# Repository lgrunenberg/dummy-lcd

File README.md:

dummy-lcd
=========

Files for using the Sony Vivaz Active Dummy LCD

TODO:
  - completely remove Arduino dependencies ( e.g. direct port access instead of pin numbers)
  - TODOs annotated in certain files

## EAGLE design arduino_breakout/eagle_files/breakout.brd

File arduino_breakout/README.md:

Breakout board for Arduino Mega + Example Code

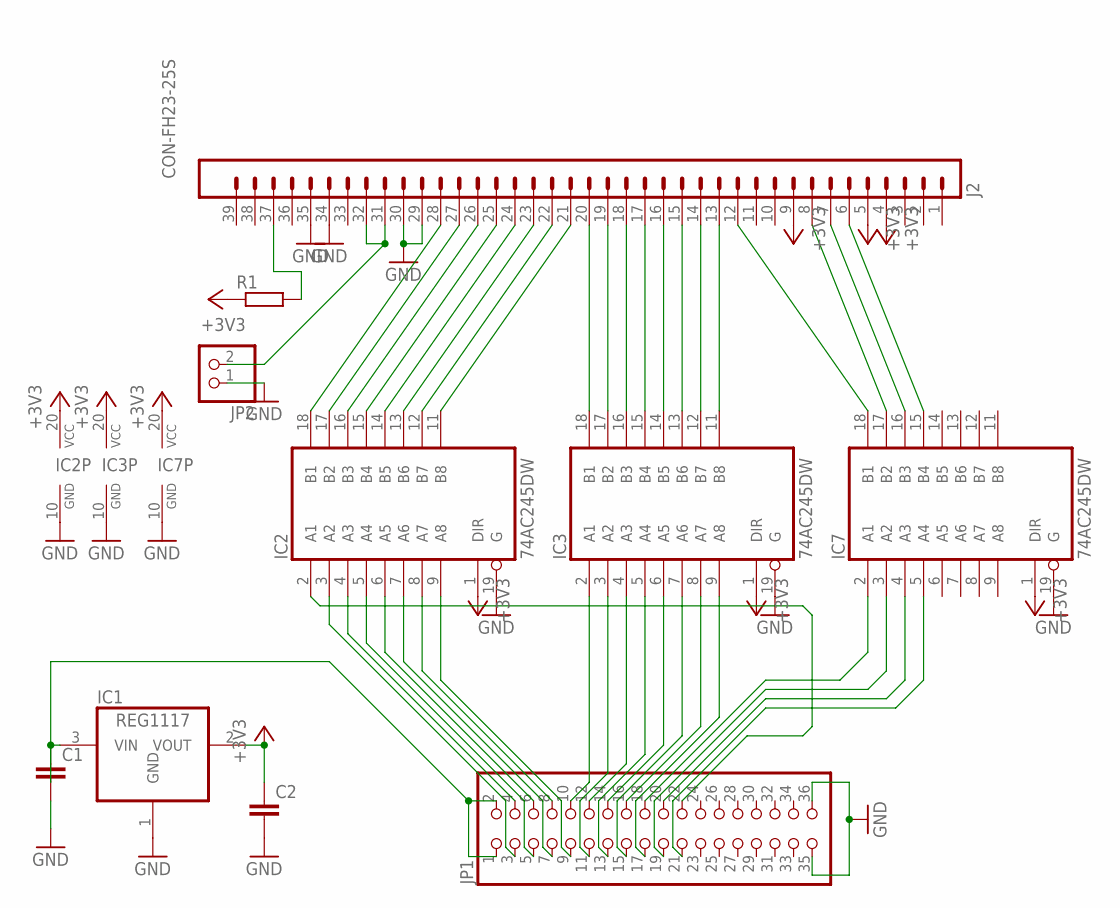
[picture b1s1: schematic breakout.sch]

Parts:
C1, C2: C-EUC0805; C0805
IC1: REG1117; SOT223
IC2, IC3, IC7: 74AC245DW; SO20W
J2: CON-FH23-25S; FH23-25S
JP1: PINHD-2X18; 2X18
JP2: PINHD-1X2; 1X02
R1: R-EU_R0805; R0805

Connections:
+3V3: C2.1, IC1.2 (VOUT), IC2.1 (DIR), IC2.20 (VCC), IC3.1 (DIR), IC3.20 (VCC), IC7.1 (DIR), IC7.20 (VCC), J2.4, J2.5, J2.9, R1.1
GND: C1.2, C2.2, IC1.1 (GND), IC2.10 (GND), IC2.19 (G), IC3.10 (GND), IC3.19 (G), IC7.10 (GND), IC7.19 (G), J2.29, J2.30, J2.34, J2.35, JP1.35, JP1.36, JP2.1
unnamed: IC2.11 (B8), J2.21
unnamed: IC2.12 (B7), J2.22
unnamed: IC2.13 (B6), J2.23
unnamed: IC2.14 (B5), J2.24
unnamed: IC2.15 (B4), J2.25
unnamed: IC2.16 (B3), J2.26
unnamed: IC2.17 (B2), J2.27
unnamed: IC2.18 (B1), J2.28
unnamed: IC3.11 (B8), J2.13
unnamed: IC3.12 (B7), J2.14
unnamed: IC3.13 (B6), J2.15
unnamed: IC3.14 (B5), J2.16
unnamed: IC3.15 (B4), J2.17
unnamed: IC3.16 (B3), J2.18
unnamed: IC3.17 (B2), J2.19
unnamed: IC3.18 (B1), J2.20
unnamed: IC7.18 (B1), J2.12
unnamed: IC7.17 (B2), J2.8
unnamed: IC7.16 (B3), J2.7
unnamed: IC7.15 (B4), J2.6
unnamed: IC2.4 (A3), JP1.4
unnamed: IC2.6 (A5), JP1.6
unnamed: IC2.8 (A7), JP1.8
unnamed: IC3.2 (A1), JP1.10
unnamed: IC2.3 (A2), JP1.3
unnamed: IC2.5 (A4), JP1.5
unnamed: IC2.7 (A6), JP1.7
unnamed: IC2.9 (A8), JP1.9
unnamed: IC3.3 (A2), JP1.11
unnamed: IC3.4 (A3), JP1.12
unnamed: IC3.5 (A4), JP1.13
unnamed: IC3.6 (A5), JP1.14
unnamed: IC3.7 (A6), JP1.15
unnamed: IC3.8 (A7), JP1.16
unnamed: IC3.9 (A8), JP1.17
unnamed: IC7.2 (A1), JP1.18
unnamed: IC7.3 (A2), JP1.19
unnamed: IC7.4 (A3), JP1.20
unnamed: IC7.5 (A4), JP1.21
unnamed: IC2.2 (A1), JP1.22
unnamed: J2.37, R1.2
unnamed: J2.31, J2.32, JP2.2
unnamed: C1.1, IC1.3 (VIN), JP1.1, JP1.2

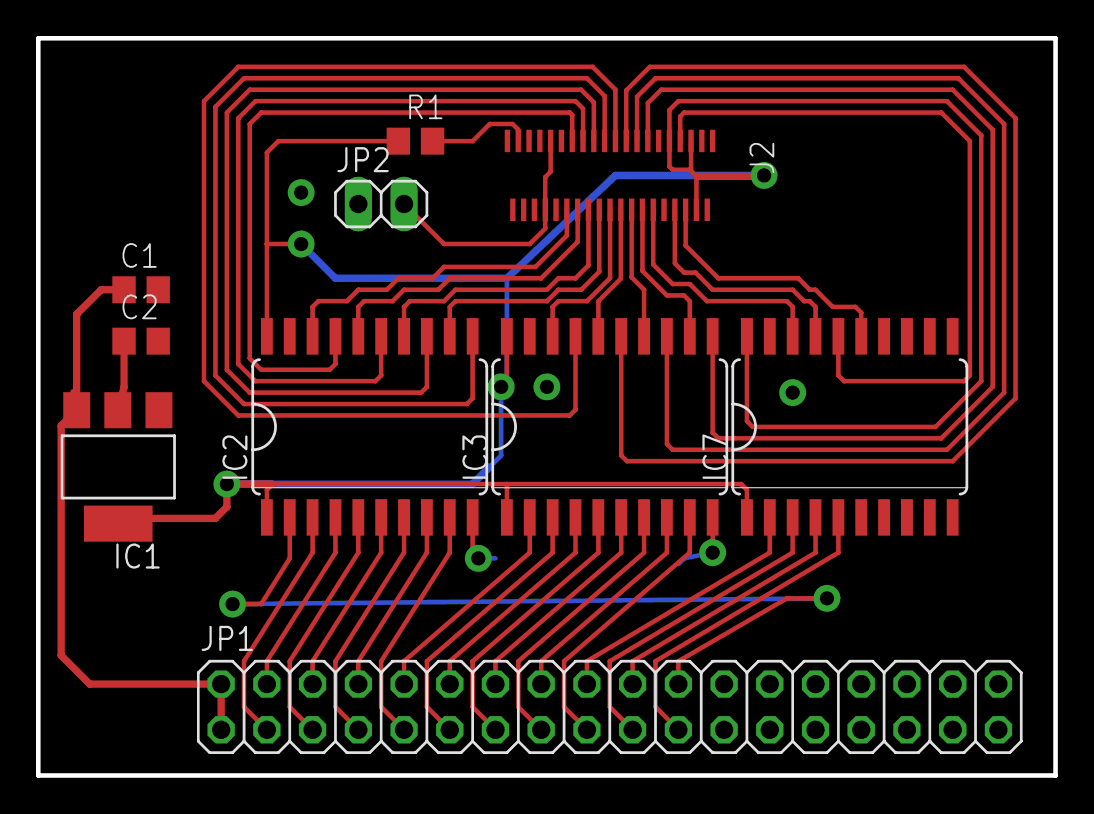
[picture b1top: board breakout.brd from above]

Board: 2 copper layers, 56.5 x 41.0 mm, 10 parts (0 on the bottom side), 45 nets.

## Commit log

2013-10-30 Removed Arduino Pin Writes
2014-01-04 Create LICENSE
